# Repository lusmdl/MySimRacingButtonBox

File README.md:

# Sim Racing Button Box

Welcome to the Sim Racing Button Controller repository!  

This project is built around an ATmega328P microcontroller, which is configured to manage a button matrix tailored for sim racing setups. 
The system uses I2C communication, where the Arduino Micro acts as the **master** and the ATmega328P functions as the **slave** (Address standard 8).
This ensures precise control and synchronization between the components.  

The ATmega328P transmits a 16-bit signal representing the states of up to 16 buttons **only when requested by the Arduino Micro**. This on-demand communication minimizes latency and ensures efficient data transfer. Additionally, the PCB includes support for a joystick connection, expanding its versatility.  

This project complements [MySimRacingCore](https://github.com/lusmdl/MySimRacingCore), which serves as the brain of the entire sim racing system. Together, they deliver a modular and high-performance solution for sim racing enthusiasts.

## Features

- Support for up to 16 buttons in a matrix configuration
- Seamless I2C communication with the Arduino Micro for precise control
- Fast and effective button state management with Keypad Library
- Joystick integration via the PCB's RJ45 jack, reducing wiring complexity

## Getting Started

### Hardware Requirements

- **ATmega328P Microcontroller**
- 16 Mhz Oscilator
- 12..22 pF Condansator
- 100 µF Condansator for supply stability
- **Button Matrix**: Up to 16 buttons
- **The PCBA from master project**: [MySimRacingCore](https://github.com/lusmdl/MySimRacingCore)

> Example PCB for this project

### Software Requirements

- [**PlatformIO**](https://platformio.org/install/ide?install=vscode): Used for programming the ATmega328P microcontroller.
- [**Wire.h**](https://www.arduino.cc/en/Reference/Wire): for I2C communication
- [**AVR Lib**](https://github.com/avrdudes/avr-libc.git): standard lib with PlatformIO.
- [**Keypad Library**](https://github.com/Chris--A/Keypad.git): Used for the 4x4 Matrix

### Software Installation and Setup

> You can either use the precompiled HEX file or compile the firmware yourself.

1. **Install PlatformIO**  
   - Set up PlatformIO in your preferred development environment (e.g., VSCode or Atom) by following the official [installation guide](https://platformio.org/install).  

2. **Clone the Repository**  

   ```sh
   git clone https://github.com/lusmdl/MySimRacingButtonBox.git
   ```  

**3. Open the Project**  
- Open the cloned repository in your PlatformIO environment.  
- Update the line `#define I2C_ADDR            8` in [ProjectConfig.hpp](/include/ProjectConfig.hpp) to match your I²C master device configuration.

> The default address is 8. If you intend to connect this device twice, use addresses 8 and 9. The master will handle the rest.

4. **Build and Upload**  
   - Prepare your ATmega328P-based PCB for flashing. It’s recommended to first flash the firmware onto an Arduino Uno and then transfer the chip to your custom environment.  
   - Build and upload the code using PlatformIO:  

   ```sh
   pio run --target upload
   ```  

### Hardware Setup

1. Assemble the PCB according to the provided design.  
2. Ensure all components, such as the button matrix and joystick, are correctly connected.

## Usage

1. **Hardware Connection**  
   - Connect the button matrix to the ATmega328P as per the configuration.  
   - Establish an I2C connection between the ATmega328P and the Arduino Micro.  

2. **Running the Firmware**  
   - Power on your system.  
   - The ATmega328P will only send a 16-bit signal to the Arduino Micro when requested over I2C, ensuring efficient communication.

## Documentation

- **Software**: [doc/software/html/index.html](doc/software/html/index.html)

## Contributing

We welcome contributions from the community!

First, read the [general contributing conventions for projects from me](CONTRIBUTING.md).

1. Fork the repository.
2. Create a new branch (`git checkout -b feature-branch`).
3. Commit your changes (`git commit -am 'Add new feature'`).
4. Push to the branch (`git push origin feature-branch`).
5. Create a new Pull Request.

## License

This project is licensed under the MIT License - see the [LICENSE](LICENSE) file for details.

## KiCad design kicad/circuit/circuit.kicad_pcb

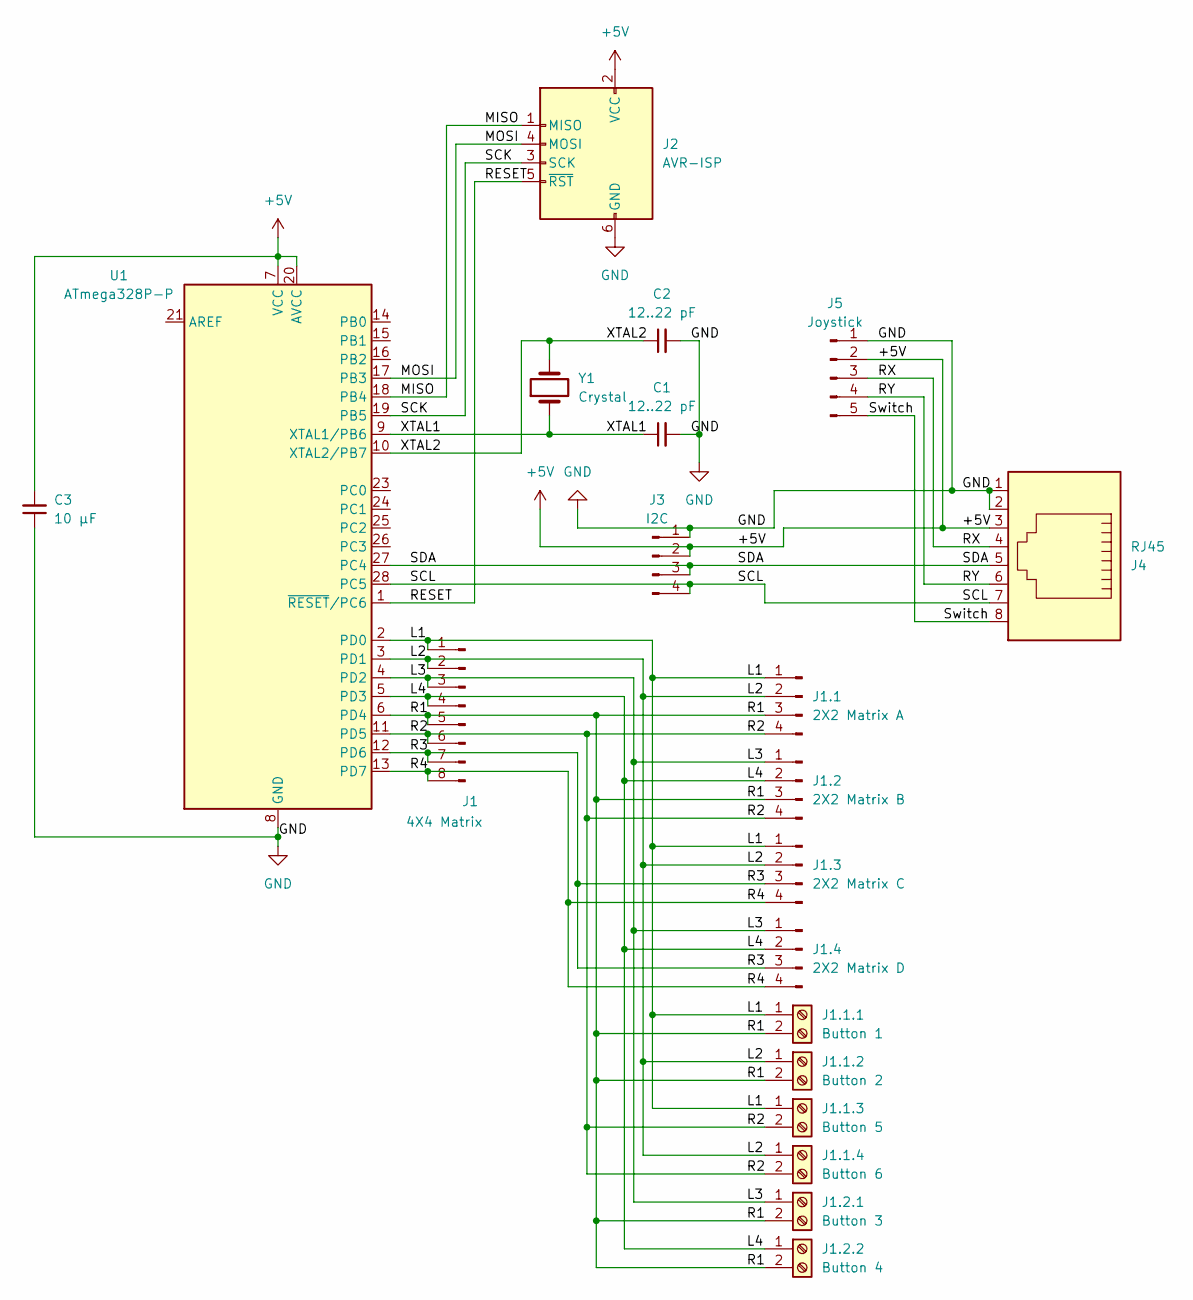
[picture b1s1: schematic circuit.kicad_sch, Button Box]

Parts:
C1, C2: 12..22 pF; C_0402_1005Metric
C3: 10 µF; C_1206_3216Metric
J1: 4X4 Matrix; PinHeader_2x04_P2.54mm_Vertical_SMD
J1.1: 2X2 Matrix A; PinHeader_2x02_P2.54mm_Vertical_SMD
J1.1.1: Button 1; TerminalBlock_Xinya_XY308-2.54-2P_1x02_P2.54mm_Horizontal
J1.1.2: Button 2; TerminalBlock_Xinya_XY308-2.54-2P_1x02_P2.54mm_Horizontal
J1.1.3: Button 5; TerminalBlock_Xinya_XY308-2.54-2P_1x02_P2.54mm_Horizontal
J1.1.4: Button 6; TerminalBlock_Xinya_XY308-2.54-2P_1x02_P2.54mm_Horizontal
J1.2: 2X2 Matrix B; PinHeader_2x02_P2.54mm_Vertical_SMD
J1.2.1: Button 3; TerminalBlock_Xinya_XY308-2.54-2P_1x02_P2.54mm_Horizontal
J1.2.2: Button 4; TerminalBlock_Xinya_XY308-2.54-2P_1x02_P2.54mm_Horizontal
J1.3: 2X2 Matrix C; PinHeader_2x02_P2.54mm_Vertical_SMD
J1.4: 2X2 Matrix D; PinHeader_2x02_P2.54mm_Vertical_SMD
J2: AVR-ISP; PinHeader_2x03_P2.54mm_Vertical_SMD
J3: I2C; PinHeader_2x02_P2.54mm_Vertical_SMD
J4: RJ45; RJ45_Molex_0855135013_Vertical
J5: Joystick; PinHeader_2x03_P2.54mm_Vertical_SMD
U1: ATmega328P-P; DIP-28_W7.62mm
Y1: Crystal; Crystal_HC18-U_Vertical

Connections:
+5V: C3.2, J2.2 (VCC), J3.2, J4.3, J5.2, U1.7 (VCC), U1.20 (AVCC)
/L1: J1.1, J1.1.1, J1.1.1.1, J1.1.3.1, J1.3.1, U1.2 (PD0)
/L2: J1.2, J1.1.2, J1.1.2.1, J1.1.4.1, J1.3.2, U1.3 (PD1)
/L3: J1.3, J1.2.1, J1.2.1.1, J1.4.1, U1.4 (PD2)
/L4: J1.4, J1.2.2, J1.2.2.1, J1.4.2, U1.5 (PD3)
/MISO: J2.1 (MISO), U1.18 (PB4)
/MOSI: J2.4 (MOSI), U1.17 (PB3)
/R1: J1.5, J1.1.3, J1.1.1.2, J1.1.2.2, J1.2.3, J1.2.1.2, J1.2.2.2, U1.6 (PD4)
/R2: J1.6, J1.1.4, J1.1.3.2, J1.1.4.2, J1.2.4, U1.11 (PD5)
/R3: J1.7, J1.3.3, J1.4.3, U1.12 (PD6)
/R4: J1.8, J1.3.4, J1.4.4, U1.13 (PD7)
/RESET: J2.5 (~RST), U1.1 (~RESET/PC6)
/RX: J4.4, J5.3
/RY: J4.6, J5.4
/SCK: J2.3 (SCK), U1.19 (PB5)
/SCL: J3.4, J4.7, U1.28 (PC5)
/SDA: J3.3, J4.5, U1.27 (PC4)
/Switch: J4.8, J5.5
/XTAL1: C1.1, U1.9 (XTAL1/PB6), Y1.1
/XTAL2: C2.1, U1.10 (XTAL2/PB7), Y1.2
GND: C1.2, C2.2, C3.1, J2.6 (GND), J3.1, J4.1, J4.2, J5.1, U1.8 (GND), U1.22 (GND)

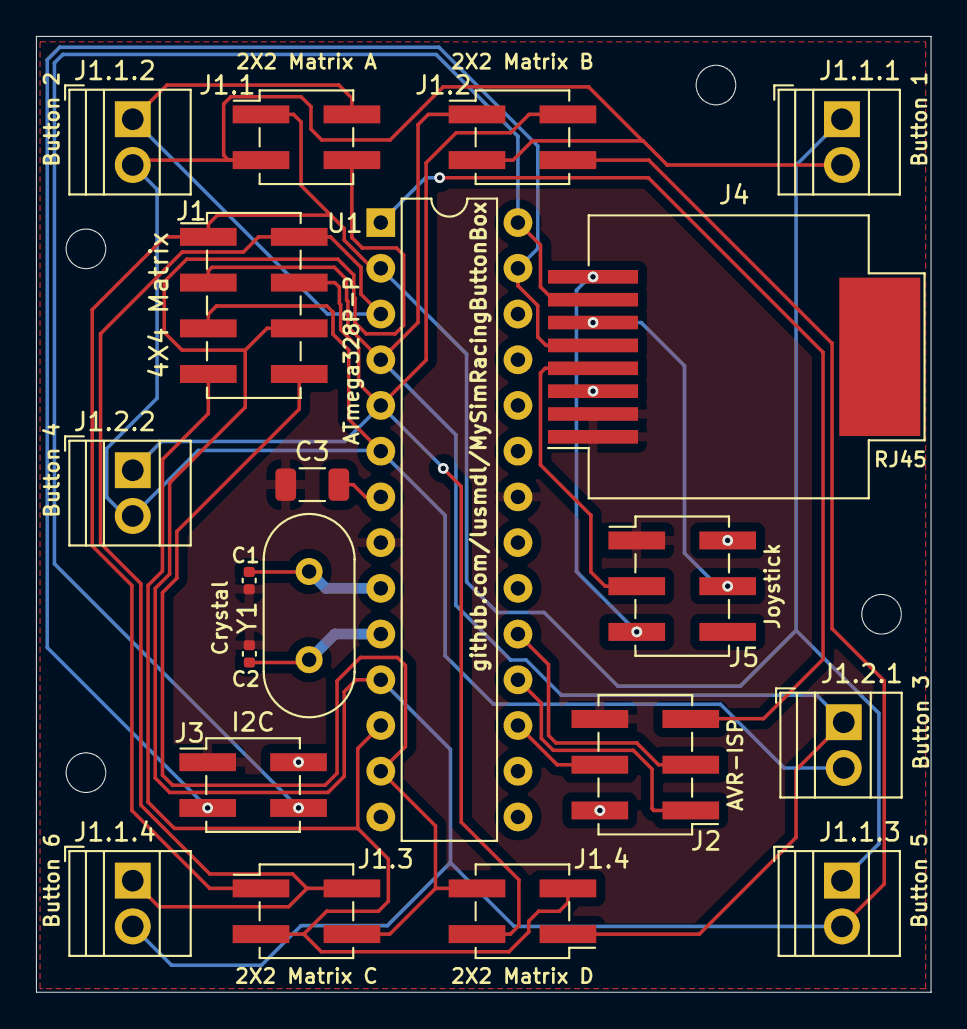
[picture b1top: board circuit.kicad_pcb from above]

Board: 2 copper layers, 49.7 x 53.1 mm, 20 parts (0 on the bottom side), 21 nets.

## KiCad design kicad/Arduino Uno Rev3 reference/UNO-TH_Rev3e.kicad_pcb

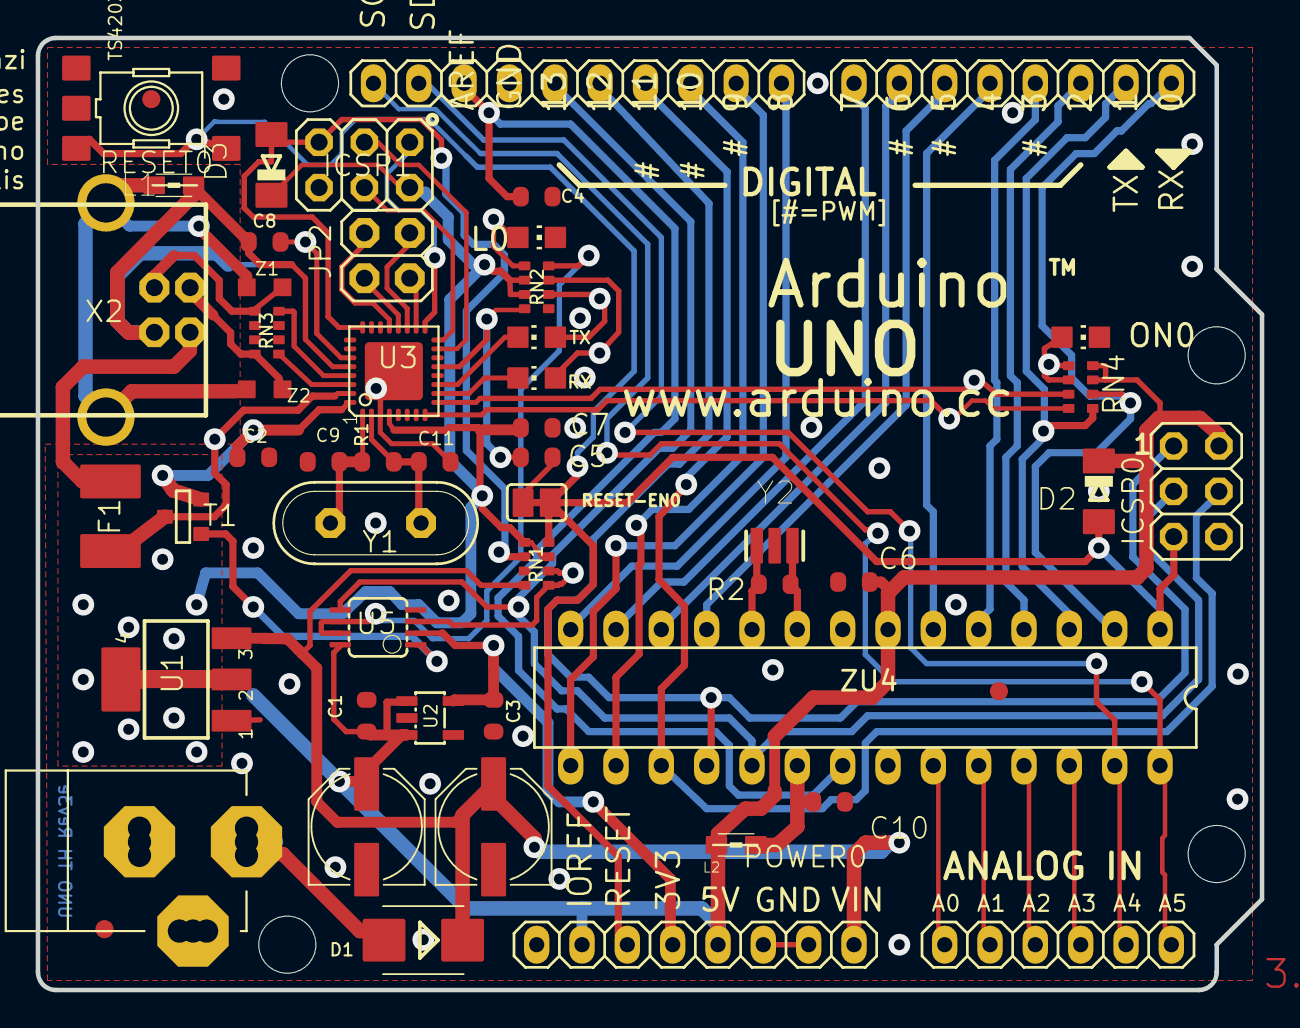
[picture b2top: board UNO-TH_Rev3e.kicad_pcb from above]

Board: 2 copper layers, 68.6 x 53.3 mm, 120 parts (1 on the bottom side), 61 nets.

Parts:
@HOLE0, @HOLE1, @HOLE2, @HOLE3: (no value)
AD0: 6x1F-H8.5; 1X06
C1, C2, C4, C5, C6, C7, C10: 100n; C0603-ROUND
C3, C8: 1u; C0603-ROUND
C9, C11: 22p; C0603-ROUND
D1: M7; SMB
D2, D3: CD1206-S01575; MINIMELF
F1: MF-MSMF050-2 500mA; L1812
FD1, FD2, FD3: FIDUCIALMOUNT; FIDUCIA-MOUNT
FRAME1: DNP; FRAME
GND_TP0, GND_TP1: TP_SP; TP-SP
GROUND0: SJ
ICSP0, ICSP1: 3x2 M; 2X03
IOH0: 10x1F-H8.5; 1X10
IOL0: 8x1F-H8.5; 1X08
JP2: 2x2 M - NM; 2X02
L0: YELLOW; CHIP-LED0805
L1: BLM21; 0805
L2: 10uH; 0805
ON0: GREEN; CHIP-LED0805
ORIGIN0: TP_SP; TP-SP
PC1, PC2: 47u; PANASONIC_D
POWER0: 8x1F-H8.5; 1X08
R1, R2: 1M; R0603-ROUND
RESET0: TS42031-160R-TR-7260; TS42
RESET-EN0: SJ
RN1: 10K; CAY16
RN2, RN4: 1K; CAY16
RN3: 22R; CAY16
RX0: YELLOW; CHIP-LED0805
T1: FDN340P; SOT-23
TP_0, TP_1, TP_2, TP_3, TP_3V3, TP_4, TP_5, TP_5V0, TP_5V1, TP_6, TP_7, TP_8, TP_9, TP_10, TP_11, TP_12, TP_13: TP_SP; TP-SP
TP_A0, TP_A1, TP_A2, TP_A3, TP_A4, TP_A5: TP_SP; TP-SP
TP_AREF0: TP_SP; TP-SP
TP_CMP0: TP_SP; TP-SP
TP_D+0: TP_SP; TP-SP
TP_D-0: TP_SP; TP-SP
TP_DTR0: TP_SP; TP-SP
TP_GATE0: TP_SP; TP-SP
TP_LCMD0: TP_SP; TP-SP
TP_LL0: TP_SP; TP-SP
TP_MISO2: TP_SP; TP-SP
TP_MOSI2: TP_SP; TP-SP
TP_ONL0: TP_SP; TP-SP
TP_PB4, TP_PB5, TP_PB6, TP_PB7: TP_SP; TP-SP
TP_PWRIN0: TP_SP; TP-SP
TP_RESET0, TP_RESET2: TP_SP; TP-SP
TP_RX0: TP_SP; TP-SP
TP_RXL0: TP_SP; TP-SP
TP_SCK2: TP_SP; TP-SP
TP_SCL0: TP_SP; TP-SP
TP_SDA0: TP_SP; TP-SP
TP_TX0: TP_SP; TP-SP
TP_TXL0: TP_SP; TP-SP
TP_UGND0: TP_SP; TP-SP
TP_USBVCC0: TP_SP; TP-SP
TP_USH0: TP_SP; TP-SP
TP_VIN0: TP_SP; TP-SP
TP_VUCAP0: TP_SP; TP-SP
TP_XT1, TP_XT2, TP_XT3, TP_XT4: TP_SP; TP-SP
TP_XUSB0: TP_SP; TP-SP
TX0: YELLOW; CHIP-LED0805
U1: NCP1117ST50T3G; SOT223
U2: LP2985-33DBVR; SOT23-DBV
U3: ATMEGA16U2-MU(R); MLF32
U5: LMV358IDGKR; MSOP08
X1: POWERSUPPLY_DC21MMX; POWERSUPPLY_DC-21MM
X2: USB-B_TH; PN61729
Y1: 16MHz; QS
Y2: CSTCE16M0V53-R0 16MHZ; RESONATOR
Z1, Z2: CG0603MLC-05E; CT_CN0603
ZU4: ATMEGA328P-PU; DIL28-3

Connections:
+3V3: C3.2, POWER0.4, TP_3V3.X, U2.5, U5.2
+5V: C1.2, C2.2, C6.2, C7.1, D2.C, D3.C, ICSP0.2, ICSP1.2, L2.1, PC2.+, POWER0.2, POWER0.5, RN1.3, RN1.5, RN2.2, RN2.3, RN4.3, RN4.4, T1.2, TP_5V0.X, TP_5V1.X, U1.2, U1.4, U2.1, U2.3, U3.4, U3.32, U5.8, ZU4.7
AD0: AD0.1, TP_A0.X, ZU4.23
AD1: AD0.2, TP_A1.X, ZU4.24
AD2: AD0.3, TP_A2.X, ZU4.25
AD3: AD0.4, TP_A3.X, ZU4.26
AD4/SDA: AD0.5, IOH0.9, TP_A4.X, TP_SDA0.X, ZU4.27
AD5/SCL: AD0.6, IOH0.10, TP_A5.X, TP_SCL0.X, ZU4.28
AREF: C4.2, IOH0.8, TP_AREF0.X, ZU4.21
AVCC: C10.2, L2.2, ZU4.20
CMP: RN1.1, RN1.2, TP_CMP0.X, U5.3
D+: RN3.5, TP_D+0.X, X2.3, Z1.1
D-: RN3.8, TP_D-0.X, X2.2, Z2.1
DTR: C5.1, RN2.4, TP_DTR0.X, U3.13
GATE_CMD: T1.3, TP_GATE0.X, U5.1
GND: C1.1, C2.1, C3.1, C4.1, C6.1, C7.2, C9.2, C10.1, C11.2, GND_TP0.X, GND_TP1.X, GROUND0.1, ICSP0.6, ICSP1.6, IOH0.7, L0.C, ON0.C, PC1.-, PC2.-, POWER0.6, POWER0.7, RESET0.1, RESET0.2, RN1.7, RN2.5, U1.1, U2.2, U3.3, U3.33, U5.4, X1.1, X1.3, Y2.2, ZU4.8, ZU4.22
IO0: IOL0.1, RN4.2, TP_0.X, ZU4.2
IO1: IOL0.2, RN4.1, TP_1.X, ZU4.3
IO2: IOL0.3, TP_2.X, ZU4.4
IO3: IOL0.4, TP_3.X, ZU4.5
IO4: IOL0.5, TP_4.X, ZU4.6
IO5: IOL0.6, TP_5.X, ZU4.11
IO6: IOL0.7, TP_6.X, ZU4.12
IO7: IOL0.8, TP_7.X, ZU4.13
IO8: IOH0.1, TP_8.X, ZU4.14
IO9: IOH0.2, TP_9.X, ZU4.15
L13: RN2.8, TP_LCMD0.X, U5.6, U5.7
M8RXD: RN4.7, TP_RX0.X, U3.9
M8TXD: RN4.8, TP_TX0.X, U3.8
MISO: ICSP0.1, IOH0.5, TP_12.X, ZU4.18
MISO2: ICSP1.1, TP_MISO2.X, U3.17
MOSI: ICSP0.4, IOH0.4, TP_11.X, ZU4.17
MOSI2: ICSP1.4, TP_MOSI2.X, U3.16
unnamed: L0.A, RN2.1, TP_LL0.X
unnamed: ON0.A, RN4.5, RN4.6, TP_ONL0.X
unnamed: RN2.7, RX0.A, TP_RXL0.X
unnamed: RN2.6, TP_TXL0.X, TX0.A
PB4: JP2.1, TP_PB4.X, U3.18
PB5: JP2.3, TP_PB5.X, U3.19
PB6: JP2.2, TP_PB6.X, U3.20
PB7: JP2.4, TP_PB7.X, U3.21
PWRIN: D1.A, TP_PWRIN0.X, X1.2
RD+: RN3.4, U3.29
RD-: RN3.1, U3.30
RESET: C5.2, D2.A, ICSP0.5, POWER0.3, RESET0.3, RESET0.4, RESET-EN0.1, RESET-EN0.2, RN1.4, TP_RESET0.X, ZU4.1
RESET2: D3.A, ICSP1.5, RN1.6, TP_RESET2.X, U3.24
RXLED: RX0.C, U3.10
SCK: ICSP0.3, IOH0.6, TP_13.X, U5.5, ZU4.19
SCK2: ICSP1.3, TP_SCK2.X, U3.15
SS: IOH0.3, TP_10.X, ZU4.16
TP_VUCAP: C8.1, TP_VUCAP0.X, U3.27
TXLED: TX0.C, U3.11
UGND: C8.2, GROUND0.2, L1.1, TP_UGND0.X, U3.28, X2.4
USBVCC: F1.1, T1.1, TP_USBVCC0.X, U3.31
USHIELD: L1.2, TP_USH0.X, X2.P$1, X2.P$2, Z1.2, Z2.2
VIN: D1.C, PC1.+, POWER0.8, RN1.8, TP_VIN0.X, U1.3
XT1: C9.1, R1.1, TP_XT3.X, U3.1, Y1.2
XT2: C11.1, R1.2, TP_XT4.X, U3.2, Y1.1
XTAL1: R2.1, TP_XT1.X, Y2.3, ZU4.9
XTAL2: R2.2, TP_XT2.X, Y2.1, ZU4.10
XUSB: F1.2, TP_XUSB0.X, X2.1

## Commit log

2024-07-15 new folder name
2024-07-15 add button.h
2024-07-16 add the circuit and pcb
2024-07-18 first test runs good in arduino uno envirement
2024-07-18 Create LICENSE
2024-07-19 add some comments and update pcb
2024-07-19 fix readme
2024-07-19 update debug definition
2024-07-19 update circuit
2024-12-21 finish PCBA
2024-12-22 refactor pcb
2024-12-23 refactor pcb + generate doxygen file comments (not finished) + new folders + firmwareexport v1.1.0
2024-12-23 add contributing file
2024-12-23 update contributing file
2024-12-23 add documentation
2024-12-23 finaly (hopefully) update readme
2024-12-23 update documentation
2024-12-23 update doc
2024-12-23 update contributing
2024-12-25 add i2c header
2024-12-25 update pcba picture
2024-12-26 add joystick connecting over rj45
2024-12-27 update pcb and documentation
2025-01-14 update Fertigungsdaten
2025-01-16 add rj45 datasheet
2025-02-07 generate firmware
2025-05-10 generate doxygen
2025-05-10 generate hex firmware v1.1.1
2025-05-10 update pcb to Rev v1.1.1 (no changes)
2025-05-10 save doxyfile
